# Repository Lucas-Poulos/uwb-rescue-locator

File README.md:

# UWB Rescue Locator

Repo: https://github.com/Lucas-Poulos/uwb-rescue-locator

A two-board UWB positioning system for a rescue/safety use case: a
**wristband** worn by a person, and a fixed **bay station** that locates it
in 3D from four anchor points and reports it over Bluetooth LE to a nearby
laptop.

Positioning is a **hybrid of two-way ranging and TDoA**, not symmetric
multilateration. A center anchor ranges to the tag for distance; three outer
anchors timestamp the same tag transmission and give direction from the
arrival-time differences. The four anchors are **not interchangeable** --
see [`docs/positioning.md`](docs/positioning.md), which is the document to
read first if you're working on anchors, clocking, coax, or connectors.

## Getting started (new contributor setup)

### 1. Install KiCad

The team standard is **KiCad 10.0.5** (see Toolchain below for why).

- **macOS**: `brew install --cask kicad` (Homebrew). If KiCad is already
  installed some other way, add `--force` to overwrite it.
- **Windows/Linux**: download the installer for your platform from
  https://www.kicad.org/download/.

You do **not** need to set any environment variables or configure library
paths yourself -- both boards' `fp-lib-table`/`sym-lib-table` use
`${KIPRJMOD}`-relative paths into this repo's own `shared/` and `libs/`
folders, so cloning the repo anywhere and opening a project just works.

The very first time you launch the KiCad GUI on a given machine, it may
offer to set up its own default global libraries (Device, Connector, etc.)
-- accept the defaults. This is a one-time, per-machine, KiCad-level setup
step, unrelated to this repo.

### 2. Get repo access and clone it

Ask whoever's administering the repo to add you as a collaborator (repo
link at the top of this file), then:

```
git clone git@github.com:Lucas-Poulos/uwb-rescue-locator.git
cd uwb-rescue-locator
```

(Use the HTTPS clone URL instead if you haven't set up an SSH key with
GitHub.)

### 3. Open a board

KiCad doesn't support one project spanning multiple PCBs, so open whichever
board you're working on directly -- there's no single top-level project
file for the whole repo:

```
open wristband/wristband.kicad_pro       # macOS; or just double-click the file
open bay-station/bay-station.kicad_pro
```

### 4. Sanity-check your setup

From a terminal, **outside** this repo (see the `kicad-cli` gotcha further
down for why):

```
cd /tmp
kicad-cli sch erc /path/to/uwb-rescue-locator/wristband/wristband.kicad_sch
```

If this reports a handful of known/expected items (see each board's sheet
table below) rather than a wall of "library not included in configuration"
errors, your KiCad install is set up correctly. If you do see that wall of
errors, see the per-major-version global library table note in Toolchain.

Before pushing anything, also read `CONTRIBUTING.md` -- branch off `main`,
don't edit a sheet someone else is actively working on, and PRs need review
(branch protection is on).

## Status (last updated 2026-11-06)

**Schematic capture is in progress on both boards.** Each board's Power/BMS
sheet is wired. The bay station's Regulation and Programming/Debug sheets
are now partially wired (grounds tied, some signal paths still open as of
2026-09-29) -- see the per-sheet table below. Everything else is still
placement-only. If you're an agent or a new teammate picking this up cold,
read this whole section before touching anything -- it's written to be a
complete handoff.

> ### Architecture change in flight: the bay station's anchors
>
> The positioning scheme was specified properly for the first time on
> 2026-09-19 (`docs/positioning.md`), and it invalidates how the bay
> station's UWB anchors are currently drawn. **Target: 10-30 cm accuracy at
> ~10 m, on Channel 5 (6489.6 MHz).**
>
> What the schematic gets wrong today:
>
> 1. **The four anchors are drawn as interchangeable peers.** They aren't --
>    one is a center anchor doing two-way ranging, three are outer anchors
>    doing TDoA against it.
> 2. **The antennas are on the board.** TDoA bearing accuracy scales with
>    baseline; a board-sized baseline gives ~17 degrees of bearing error.
>    The four antennas move onto ~1-2 m coax runs to a rigid frame.
> 3. **The DWM3000 module can't do TDoA in a multi-anchor array at all.** It
>    exposes no clock pin, so four of them cannot share a time base -- and
>    1 ns of clock error is 30 cm of position error.
>
> **The resolved architecture:** four discrete **DW3210** ICs on the one PCB,
> sharing a single 38.4 MHz TCXO through a 1:4 low-skew buffer, with the four
> antennas remote on coax. This makes synchronization *structurally absent*
> rather than solved -- no drift model, no sync firmware -- and moves the cost
> into the RF path, where CH5's ~17 dB of link margin absorbs it.
>
> Going discrete adds an RF front-end and a controlled-impedance stackup. It
> also loses the module's pre-certified status -- which **does not matter
> here**: this is a university prototype, not marketed or sold, so it doesn't
> go through FCC/CE testing. That was the single largest cost of going
> discrete, and it's now off the table. See `docs/decisions.md`.
>
> The remaining critical-path item is **array calibration**, which the design
> genuinely does not close without.
>
> **The wristband is unaffected by the clock problem** -- a single transceiver
> has nothing to synchronize against. It has separately consolidated onto a
> single DWM3001C; see its own README.

### What exists, per board

The wristband has 7 hierarchical sheets, the bay station 10. Reference designators are
project-wide unique per board (checked, no collisions) -- see each
`libs/components.csv` for the full part-by-part BOM.

**Wristband** (`wristband/`):
| Sheet | Status | Contents |
|---|---|---|
| Power BMS | **Wired** (global labels, no drawn wires), ERC clean (0 errors, 1 cosmetic warning) | JST-PH battery -> AO3401A reverse-polarity FET -> TVS -> DW01A+FS8205A protection -> MCP73831 charger (USB-C in) |
| Radio MCU | Placement only, not wired | DWM3001C (U3) + decoupling. One module: DW3110 UWB + nRF52833 MCU + accelerometer + both antennas |
| Mechanical | Placement only | 4x M2 mounting holes |
| Regulation | Placement only, not wired | MCP1700T-3302E/TT LDO (3.3V) -- battery hits 4.2V, DWM3001C tops out at 3.6V |
| Programming/Debug | Placement only, not wired | ARM Cortex Debug SWD header, targeting the nRF52833 inside U3 |
| Indicators | Placement only | Status LEDs: D2 charge (MCP73831 STAT) + D3 system (nRF52833 GPIO) |
| Test Points | Placement only, **new** | TP1-TP5: both rails, 2x GND, firmware timing marker |

**Bay Station** (`bay-station/`):
| Sheet | Status | Contents |
|---|---|---|
| Power BMS | **Wired** (global labels), ERC has 8 known/expected items (see `power_bms_notes.md`) | Barrel jack + USB-C power-only input -> MCP73871 power-path charger -> MAX17048 fuel gauge; separate backup-battery input with its own AO3401A reverse-polarity FET + TVS |
| Connectivity | Placement only, not wired | Fanstel BT840 (U3, nRF52840) + decoupling. Symbol authored from the real datasheet |
| UWB Array | Placement only, not wired | 4x DW3210 (U4=A0 center, U5-U7=A1-A3 outer) + GPIO5/6 straps (R10-R17) + IRQ pulldowns (R25-R28) + full per-anchor decoupling from Qorvo Figure 32 (C40-C74, FB1-FB4 beads, R33-R36 RF2 terminations) |
| Mechanical | Placement only | 4x M3 mounting holes |
| Regulation | **Partially wired** (11 wires, 3 junctions, 5 GND symbols added 2026-09-29); U8's VIN, EN, and PG still unconnected (ERC) | TPS62A02PDDCR buck converter -- steps the unregulated `+VSYS` rail down to a safe ~3.3V for the BT840 host and the DW3210 anchors |
| Clock Distribution | Placement only, **new** | Shared 38.4MHz reference for the 4x DW3210 array: AC-coupling + XTO caps placed, TCXO/buffer TBD |
| Indicators | Placement only | Status LEDs: D4 charging, D5 charge-done, D6 power-good (all MCP73871), D7 system (host GPIO) |
| Test Points | Placement only | TP1-TP21: rails, 2x GND, TCXO + 4x anchor clock, SPI bus, reset, per-anchor CS x4 + IRQ x4 |
| GNSS / Orientation | Placement only, **new** | MAX-M10S GNSS (U9) + LIS3MDL magnetometer (U10) + LIS2DH accelerometer (U11) -- georeferences the array |
| Programming/Debug | Placement only in practice (1 wire, 1 junction, 1 GND symbol added 2026-09-29 -- just the ground tie) | **Rebuilt for Nordic**: SWD header (J3) + RESET button (SW2), both still fully unwired per ERC. ESP32 circuitry and the second USB-C deleted |

"Placement only" sheets deliberately show a lot of ERC "not connected"/"not
driven" warnings -- that's expected, not a bug, until they get wired.

### Confirmed chips/ICs (all sourced against real datasheets, not guessed)

| Part number | Role | Board(s) | Qty |
|---|---|---|---|
| Qorvo **DWM3001C** | UWB transceiver + nRF52833 MCU + LIS2DH12 accelerometer + both antennas, one module. Replaced NINA-B111 + DWM3000 + the antenna sheet | Wristband | 1 |
| Qorvo **DW3210** | Discrete UWB transceiver IC, QFN-40 5x5mm. One per anchor (U4=A0 center, U5-U7=A1-A3 outer). Chosen over the DWM3000 module because the module exposes no clock pin, and a shared reference is what makes the TDoA array work -- see `docs/positioning.md` | Bay Station | 4 |
| Qorvo **DWM3000** | UWB transceiver module. **No longer used on either board** -- the wristband moved to the DWM3001C and the bay station to discrete DW3210. Symbol and footprint are retained in `shared/` for reference only | -- | 0 |
| Microchip **MCP73831** | LiPo linear battery charger | Wristband | 1 |
| Fortune Semiconductor **DW01A** | Battery protection IC | Wristband | 1 |
| Fortune Semiconductor **FS8205** (commonly sold as "FS8205A" -- see `wristband/libs/README.md`) | Protection dual MOSFET, DW01A's partner IC | Wristband | 1 |
| AOS **AO3401A** | Reverse-battery-polarity protection P-MOSFET ("ideal diode") | Wristband + Bay Station | 2 |
| onsemi **ESD5B5.0ST1G** | TVS diode, battery/power-input protection | Wristband (1) + Bay Station (2) | 3 |
| Fanstel **BT840** (Nordic nRF52840) | Host MCU + BLE link to a laptop. Replaced ESP32-S3-WROOM-1 once the WiFi/internet requirement was dropped | Bay Station | 1 |
| Microchip **MCP73871** | Charge management + power-path IC | Bay Station | 1 |
| Maxim/Analog Devices **MAX17048** | Battery fuel gauge (SOC monitor) | Bay Station | 1 |
| Microchip **MCP1700T-3302E/TT** | LDO regulator (3.3V) -- battery rail can hit 4.2V, which exceeds the DWM3001C's 3.6V operating max without this | Wristband | 1 |
| TI **TPS62A02PDDCR** | Buck (switching) regulator -- same voltage-safety role as the wristband's LDO, sized for the bay station's higher combined load current | Bay Station | 1 |

Footprint caveats: MAX17048 is flagged `_PLACEHOLDER` in its footprint file
-- pin/electrical data is fully verified, but one land-pattern dimension
needs re-checking against the real datasheet figure before fab (see
`bay-station/libs/README.md`). The same caveat applies to the DWM3000
footprint retained in `shared/`, though nothing uses it now.

**No footprint assigned yet**: `U3` on both boards (BT840, 65 pins; and
DWM3001C, 48 pins), plus bay-station `L1` (1uH inductor -- no exact KiCad
default matches the XGL3520, pick at BOM time) and `SW2`. Not blocking
while both `.kicad_pcb` files are still empty, but it blocks layout.

Standard passive size for this whole project: **0603** for R/C/L (0-ohm
0603 link/jumper resistors are documented as a standard available option in
each `components.csv`, not yet placed on any sheet -- no specific
strap/bridge need identified yet).

Full reasoning/history for every choice above, plus the still-open
decisions (anchor placement, uplink backend, etc.), is in
`docs/decisions.md`.

### Known gotchas for whoever (human or agent) works on this next

- **kicad-cli silently fails on `extends`-based symbols.** Any cached
  schematic symbol using KiCad's `extends` mechanism (e.g. the default
  `AO3401A extends TP0610T`) makes `kicad-cli` fail to load the *entire
  file* and silently report it as empty (0 components, 0 ERC violations)
  rather than erroring loudly. Both boards work around this by embedding a
  flattened, non-`extends` copy of AO3401A. If a future sheet adds another
  `extends`-based part and ERC suspiciously shows 0 violations, check this
  first.
- **Always run `kicad-cli` from a scratch directory, never from inside a
  git repo.** It writes `.rpt` report files to the current working
  directory as a side effect; running it from inside a repo pollutes that
  repo's working tree with stray files.
- **KiCad's global library table is per-major-version and doesn't
  auto-populate from `kicad-cli` alone** -- see the Toolchain section below.
- **Don't leave a KiCad GUI window open on a project while also editing its
  files by hand/via script.** This happened once already: a background GUI
  session silently resaved `bay-station/power_bms.kicad_sch` in KiCad 10
  format while a concurrent edit was adding new sheets to the root file. No
  data was lost (verified via a reference-designator diff before
  committing), but it could have silently clobbered the newer edits if the
  stale window had been saved again afterward. Close/reload any open KiCad
  windows before doing further programmatic edits, and vice versa.
- The sibling project at `~/kicad-projects/wristband-alarm` (a *different*,
  unrelated wristband-alarm concept, also u-blox NINA-based) has its own
  long-standing uncommitted working-tree state -- don't touch it, don't
  assume its README reflects its actual working tree.

### In-flight work on GitHub (as of 2026-11-06)

Merged into `main` today: this Design Specifications section, the bay
station's power/regulation/programming-debug wiring pass, the decision not
to add an external wristband IMU (`docs/decisions.md` -- the DWM3001C's
built-in LIS2DH12 covers it), PR #9 (the bay station's missing I2C pull-ups,
R37-R39), and PR #8 (the full per-anchor DW3210 decoupling set, C40-C74 +
FB1-FB4 + R33-R36, from Qorvo's own reference design).

#8 and #9 both textually conflicted with the power-wiring pass on
`bay-station/connectivity.kicad_sch` and `uwb_array.kicad_sch` respectively,
because those files got reserialized to KiCad 10 format in between. Each was
hand-ported onto the reserialized files rather than text-merged -- see
`b7ab51f` and `4ef1099` for exactly what that involved and how it was
verified (balanced parens, no duplicate references, ERC recognizing every
new component with precisely the expected violation delta). This is the one
case where resolving a KiCad schematic conflict by hand was done carefully
and checked, not the norm -- `CONTRIBUTING.md`'s warning about silent
corruption from hand-resolving `.kicad_sch` conflicts still stands for
anything less thoroughly verified.

One PR needs a **team decision, not a merge**: **#7**
`feat/bay-station-wifi` adds an ESP32-C5 Wi-Fi co-processor and explicitly
reopens part of the 2026-09-19 "no WiFi" call (see `docs/decisions.md`,
"Bay-station Wi-Fi uplink"). Its own GPIO allocation table is marked
"PROPOSED, needs team sign-off" -- read that section before merging it.

### Not done yet (in rough next-up order)

1. **Bay station: rework the anchor design** for four discrete DW3210s on
   one board sharing a TCXO, with the antennas on coax. Blocked behind the
   open items in `docs/decisions.md` (cable loss, TCXO/buffer selection,
   array calibration) -- this is the project's critical path.
2. Wire all placement-only sheets (net labels between MCU/radio pins, their
   decoupling, the new regulator outputs, and power-rail connections in
   from Power BMS). The wristband can proceed independently of item 1.
3. ~~**Bay station: resolve the two-USB-C-connector situation**~~ -- resolved
   by the move to Nordic. The second connector existed only for ESP32-S3
   native-USB flashing; the BT840 programs over SWD, so it goes away with the
   rest of the ESP32-specific circuitry.
4. **Bay station: source a real footprint for L1** (the buck converter's
   inductor, Coilcraft XGL3520-102MEC) -- no KiCad-default match exists yet.
5. ~~Confirm/re-verify decoupling cap values against each part's exact
   datasheet application circuit~~ -- done, see `docs/passives-reference.md`.
   One passive was found missing (100k IRQ/GPIO8 pulldowns, now added to all
   5 DWM3000 instances); DWM3000's own decoupling was confirmed to exceed
   what Qorvo's minimal example circuit actually calls for (kept anyway, not
   wrong, just more conservative than strictly required).
6. ~~Antenna matching-network values~~ -- gone. The DWM3001C carries both
   antennas on-module, so `antenna.kicad_sch` was deleted along with the
   tuning task.
7. ~~Anchor placement/enclosure geometry~~ -- topology resolved (all four
   transceivers on-board, antennas remote on coax to a rigid frame, see
   `docs/positioning.md`); the remaining piece is the frame's mechanical
   design, including A0's out-of-plane offset.
8. Bay station uplink protocol -- what the laptop actually receives over BLE
   (open decision). "Backend" no longer applies: there is no server, see
   `docs/system-overview.md`.
9. PCB layout. The bay station's `.kicad_pcb` has its **4-layer
   controlled-impedance stackup** set from DW3000 Section 7.3.2 Figure 35
   (1.048mm finished) but is otherwise still genuinely empty: 0 footprints,
   no outline. Blocked upstream, same as before -- the schematic is mostly
   placement-only, so there's nothing to import yet.

   **Correction, 2026-11-06: the wristband's `.kicad_pcb` is not an empty
   stub.** It already carries 36 footprints, a routed board outline, and
   real DRC findings (100 unrouted ratsnest items, plus silkscreen/clearance
   violations) from the DWM3001C migration (PR #5, merged). U3 (the
   DWM3001C itself) has no footprint assigned yet, so it isn't among those
   36 and can't be placed until one is imported -- see the footprint-caveats
   note above.

## System overview

```
                         A1 ← antenna on coax
                            \
   ┌─────────────┐           \      ┌───────────────────────────┐
   │  Wristband   │  UWB       ○────│  Bay Station (ONE PCB)     │
   │  (worn tag)  │ ═════════▶ A0   │  4x DW3210, one TCXO       │
   └─────────────┘  one TX    / \   │  BT840 (nRF52840) host     │
                             /   \  └───────────┬────────────────┘
                           A2     A3            │ Bluetooth LE
                      antennas on ~1-2 m        ▼
                      coax, rigid frame       Laptop

   A0     two-way ranging  -> range to tag
   A1-A3  TDoA vs. A0      -> direction to tag

   All four transceivers share one clock on the board.
   Only the antennas are remote.
```

- **Wristband**: one Qorvo DWM3001C (UWB + nRF52833 MCU + antennas) +
  a compact BMS (MCP73831 charger + DW01A/FS8205 protection + AO3401A
  reverse-polarity protection). Design compromises favor small size and
  just enough battery life to get core functionality working. In the
  positioning scheme its job is simply to transmit -- one transmission
  yields all four measurements, deliberately, because the tag is the
  power-constrained side.
- **Bay station**: four UWB receivers in two roles (one center, three outer)
  on a single PCB sharing one TCXO + a Fanstel BT840 (nRF52840) host, linking
  to a laptop over BLE + a BMS designed for long runtime rather than small size
  (MCP73871 power-path charger + MAX17048 fuel gauge), since the bay station
  isn't worn. The four antennas sit on ~1-2 m coax runs to a rigid frame --
  that's what buys the baseline the bearing measurement needs.

There's no physical connector between the wristband and the bay station --
their only interface is the UWB radio link. The bay station's own antennas
are wired to it over SMA coax (CH5 at 6489.6 MHz is above U.FL's 6 GHz
rating). See `docs/system-overview.md` and `docs/positioning.md`.

## Design specifications

Quick-reference only -- full reasoning, error budgets, and datasheet
citations live in `docs/positioning.md` (RF/clock/mechanical) and
`docs/decisions.md` (every component/architecture call). Anything not listed
here as resolved is still an open decision; check there before assuming a
number is final.

**Performance target**
| | |
|---|---|
| Accuracy | 10-30 cm |
| Range | ~10 m |
| Baseline (A0-to-outer-antenna spacing) | ~1 m as built; frame size is the real limit, not cable loss |

**RF**
| | |
|---|---|
| UWB channel | Channel 5, 6489.6 MHz |
| UWB IC, bay station | 4x Qorvo DW3210 (QFN40, non-PDoA) -- U4=A0 center, U5-U7=A1-A3 outer |
| UWB IC, wristband | Qorvo DW3110 (WLCSP), inside the DWM3001C module |
| UWB connectors | SMA -- CH5 is above U.FL/W.FL/MMCX/MCX's 6 GHz rating and SMB's 4 GHz rating |
| Link budget | 86 dB available (CH5, 850 kbps, 1024-symbol preamble); ~17 dB margin at 10 m |
| Antennas (bay station) | Not yet selected -- candidates covering CH5: Taoglas UWC.01 / ILA.68 / UWCCP.01 |

**Clock (bay station array)**
| | |
|---|---|
| Reference | One 38.4 MHz TCXO -> 1:4 low-skew fan-out buffer -> all 4 DW3210 XTI pins |
| Coupling | 2200 pF AC-coupled into each XTI; 1 pF from each XTO to ground |
| TCXO spec | 0.8 V-VDD2 Vpp, -132 dBc/Hz @ 1 kHz, -145 dBc/Hz @ 10 kHz, 40-60% duty (DW3000 Datasheet Table 10) |
| TCXO + buffer part numbers | Open |

**Positioning architecture**
Hybrid two-way-ranging + TDoA, not symmetric multilateration -- see
`docs/positioning.md` for the full derivation.
| | |
|---|---|
| Center anchor (A0) | Two-way ranging with the wristband -> range |
| Outer anchors (A1-A3) | TDoA vs. A0 on the same tag transmission -> direction |
| System | 4 equations, 3 unknowns -- overdetermined by 1; use the residual as a quality metric |
| Mechanical | Rigid frame fixes geometry (no install-time survey); A0 offset 20-30 cm out of the A1-A3 plane to avoid a mirror ambiguity |
| Array calibration | Required, not optional (generic +/-6 cm spec is 3x too loose at this baseline); procedure/fixture still open |

**Power**
| | Wristband | Bay station |
|---|---|---|
| Regulator | TI TPS7A0233PDBVR LDO, 3.3V | TI TPS62A02PDDCR buck, 2A |
| Load vs. rating | ~43 mA (4.6x headroom) | ~347-682 mA depending on estimate (3-6x headroom; recheck once clock parts are chosen) |
| Standby | ~2.7 uA | n/a -- BMS optimized for runtime, not size |

**Connectivity**
| | |
|---|---|
| Wristband <-> bay station | UWB only -- one tag transmission per exchange, no other radio link |
| Bay station -> laptop | Bluetooth LE (GATT service) -- no WiFi, no internet uplink |
| Georeferencing | u-blox MAX-M10S GNSS + ST LIS3MDL magnetometer + ST LIS2DH accelerometer (bay station only; position + heading both required) |

**Cost** (one prototype pair, hobbyist qty-1 pricing -- see `docs/bom-cost.md`)
| | |
|---|---|
| Wristband | ~$67 |
| Bay station | ~$278 |
| Total | ~$345 |

**Regulatory**
No FCC/CE certification -- university prototype, not sold or deployed as a
product. Revisit as a first-class schedule item if that ever changes.

**Toolchain**
| | |
|---|---|
| KiCad | 10.0.5 (files on disk still in 8.0 format) |
| MCUs | Both Nordic -- nRF52833 (wristband, inside DWM3001C) / nRF52840 (bay station, inside the Fanstel BT840) |
| Firmware SDK | Open -- nRF5 SDK vs. Zephyr / nRF Connect SDK |

## Repo layout

```
shared/                      # symbols/footprints/3D models used on BOTH boards (e.g. the UWB IC)
  symbols/                   # shared .kicad_sym library
  footprints/                # shared .pretty footprint library
  3dmodels/                  # shared .step/.wrl models
wristband/                   # KiCad project: the wearable tag
  wristband.kicad_pro/sch/pcb
  libs/                      # wristband-only symbols/footprints
bay-station/                 # KiCad project: the fixed 4-anchor station
  bay-station.kicad_pro/sch/pcb
  libs/                      # bay-station-only symbols/footprints
docs/
  positioning.md             # the ToF + TDoA scheme, error budget, clock architecture
  system-overview.md         # block diagram + RF/data interface between the boards
  decisions.md               # open + resolved component/architecture decisions log
  passives-reference.md      # every chip's reference-design passives, compiled per-chip
  bom-cost.md                # build cost estimate for one prototype pair
firmware/                    # nRF52840 / nRF52833 firmware -- skeleton only, nothing written
CLAUDE.md                    # working rules for Claude Code / other coding agents
CONTRIBUTING.md              # git workflow, sheet conventions, pre-push checks
```

Each board is its own KiCad project (KiCad doesn't support one project
spanning multiple PCBs), but both live in this one repo so shared parts,
docs, and history stay in one place. Each project's `fp-lib-table` /
`sym-lib-table` reference the `shared/` libraries via `${KIPRJMOD}` relative
paths, so this works regardless of where the repo is cloned -- no per-machine
setup needed.

## Toolchain

Files are currently in **KiCad 8.0** format, originally authored/verified
against KiCad 8.0.6. As of 2026-08-14 this machine has been upgraded to
**KiCad 10.0.5** (the actual current stable -- confirmed as the team's
standard, superseding an earlier, since-corrected plan to target KiCad 9.x).
All existing files were re-checked with
`kicad-cli` under 10.0.5 (`sch erc`/`pcb drc`) and open/parse cleanly with no
new issues -- opening a file in the newer GUI and re-saving is still a
one-way, zero-cost upgrade whenever the team wants to bump the file format
itself; nothing has been re-saved yet, so the files on disk are still 8.0
format.

Note for anyone else upgrading KiCad's major version: `kicad-cli` alone
won't auto-populate the new version's global symbol/footprint library table
(`~/Library/Preferences/kicad/<version>/sym-lib-table` /`fp-lib-table`) --
that normally happens the first time you launch the actual KiCad GUI and it
offers to migrate/create settings. If you only ever use `kicad-cli`
headlessly without opening the GUI first, you may see a wall of spurious
"library not included in configuration" ERC errors -- just launch KiCad.app
once (or copy the two `*-lib-table` files from
`.../KiCad.app/Contents/SharedSupport/template/`) to fix it.

## Using Claude Code (or another coding agent) on this project

**The working rules for agents live in [`CLAUDE.md`](CLAUDE.md)** -- Claude
Code picks that up automatically. This section is the human-readable version
of why those rules exist.

KiCad's file formats (`.kicad_sch`, `.kicad_pcb`, `.kicad_pro`, `.kicad_sym`,
`.kicad_mod`) are plain text (S-expression or JSON) -- an agent can read and
edit them directly like any other source file, no special MCP server or
plugin required. Everything in this repo so far was built that way. A few
things make it work reliably, several of them learned the hard way in this
repo's own history:

- **`kicad-cli` is the fast headless sanity check.** After any edit, run
  `kicad-cli sch erc <board>.kicad_sch` and `kicad-cli pcb drc
  <board>.kicad_pcb` before trusting a change.
  - **macOS**: a Homebrew install symlinks it onto `PATH` automatically
    (`/opt/homebrew/bin/kicad-cli`); otherwise it's inside the app bundle at
    `/Applications/KiCad/KiCad.app/Contents/MacOS/kicad-cli`.
  - **Windows**: the official installer puts it on `PATH` automatically; if
    not, it's at `C:\Program Files\KiCad\10.0\bin\kicad-cli.exe`.
  - **Linux**: on `PATH` automatically via most package managers (apt,
    dnf, etc.) or the official AppImage/flatpak.
- **Always run `kicad-cli` from a scratch/temp directory, never from
  inside this repo.** It writes `.rpt` report files to the current working
  directory as a side effect -- running it from inside a git repo (this
  one or any other) pollutes the working tree with stray files. This has
  actually happened once already, to an unrelated sibling project, from a
  leftover `cd`.
- **`kicad-cli` silently fails on `extends`-based symbols.** A cached
  schematic symbol using KiCad's `extends` mechanism (e.g. the default
  library's `AO3401A extends TP0610T`) makes `kicad-cli` fail to load the
  *entire file* and report it as empty (0 components, 0 ERC violations)
  instead of erroring loudly -- a suspiciously clean ERC run is a red flag,
  not necessarily good news. This repo works around it everywhere by
  embedding flattened, non-`extends` copies of any such symbols (see
  `docs/decisions.md` and the various `*_notes.md` files for examples).
- **Use an existing sheet/symbol/footprint as the format template before
  writing a new one.** Every file in this repo was built by reading a
  known-good file first -- either one already in this repo, or one of
  KiCad's own bundled default libraries -- and matching its exact
  structure, rather than freehand-authoring the s-expression format from
  memory. This repo uses literal tab characters for indentation, not
  spaces; match that.
- **Don't run scripted file edits at the same time as a live KiCad GUI
  session has the same project open.** A background GUI window doesn't
  know about changes made outside it, and saving from a stale window can
  silently overwrite newer edits -- this already caused one near-miss on
  the bay station board (see "Known gotchas" above). Close/reload any open
  KiCad windows before scripted edits, and vice versa. A lock file at
  `<board>/~<board>.kicad_pro.lck` means a GUI session currently has that
  project open.
- **Verify real datasheet facts (pinouts, voltage ratings, current draw)
  by actually fetching and reading the datasheet PDF**, not from memory or
  a search-result summary -- several real bugs/gaps in this repo were only
  caught this way (e.g. the wristband's missing voltage regulator, a
  part-number that doesn't actually exist, a mislabeled SOT-23-6 part).
- **pcbnew's Python bindings** are available for programmatic
  footprint/board work (generating a blank `.kicad_pcb`, loading a
  footprint to sanity-check its pad count, etc.) via KiCad's own bundled
  Python interpreter -- **not** your system Python, which won't have the
  `pcbnew` module installed:
  - **macOS**: `/Applications/KiCad/KiCad.app/Contents/Frameworks/Python.framework/Versions/Current/bin/python3`
  - **Windows**: typically `C:\Program Files\KiCad\10.0\bin\python.exe`
  - **Linux**: usually just your system `python3` if KiCad was installed via
    a package manager that wires up the `pcbnew` module for it; otherwise
    check your distro's KiCad packaging docs.

## Will this work on both Mac and Windows?

Yes, and this has actually been checked, not just assumed:

- No absolute Mac-specific paths are baked into any `.kicad_pro`/`.kicad_sch`/
  `.kicad_pcb`/library file (`git grep`-checked) -- all cross-file/library
  references use `${KIPRJMOD}`-relative paths, which KiCad resolves
  identically on every OS.
- No filenames in this repo use characters or reserved names that are
  illegal on Windows (`: * ? " < > |`, or `CON`/`PRN`/`AUX`/`NUL`/`COM1-9`/
  `LPT1-9`), and no path exceeds even a fraction of Windows' historical
  260-character path limit (longest path in this repo is 80 characters).
- All tracked files use consistent LF line endings, and `.gitattributes`
  normalizes this going forward so a Windows contributor's git config
  (which sometimes auto-converts line endings on checkout) can't silently
  turn KiCad files into CRLF and create noisy diffs or merge pain.

What differs by platform is purely the install step and a couple of tool
paths (both covered above/in Getting Started) -- KiCad itself, the file
formats, and this repo's structure are fully cross-platform.

## Contributing

See `CONTRIBUTING.md` for the git workflow (branching, hierarchical-sheet
conventions to avoid merge conflicts, pre-push checks).

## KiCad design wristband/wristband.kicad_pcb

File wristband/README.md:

# Wristband

The worn tag. Open `wristband.kicad_pro` in KiCad.

## Scope

Deliberately minimal: **battery management plus one UWB module, and not much
else.** The tag's only job is to take part in a two-way ranging exchange with
the bay station's center anchor. Everything not needed for that is gone.

- **UWB + MCU**: Qorvo **DWM3001C** (resolved 2026-09-19) -- one module
  containing the DW3110 UWB transceiver, a Nordic nRF52833 MCU, an ST
  LIS2DH12 accelerometer, the UWB and Bluetooth antennas, power management
  and the 38.4 MHz crystal. Its datasheet states it *"requires no RF design
  as the antenna and associated analog and RF components are on the module"*.
- **BLE and the accelerometer are unused.** The tag talks only over UWB. Both
  are silicon inside a module bought for its Cortex-M4 and its UWB radio --
  they cost nothing to leave idle: no external parts, no wiring, no firmware.
  See "Worth revisiting" below.
- **BMS**: sized for "just enough" runtime -- size and weight take priority
  over battery life here, in contrast with the bay station.

Why the tag transmits once per fix: the bay station's center anchor completes
the ranging exchange, and the three outer anchors timestamp that *same*
transmission. One transmission, four measurements -- deliberately, because
the tag is the power-constrained side. See `../docs/positioning.md`.

## Status

Seven hierarchical sheets, all registered in `wristband.kicad_pro`'s `sheets`
list and wired into `wristband.kicad_sch` as sheet symbols.

| Sheet | Status | Contents |
|---|---|---|
| `power_bms` | **Wired** (global labels, no drawn wires), ERC clean | Full battery/charging/protection chain |
| `radio_mcu` | **Wired**, ERC clean | DWM3001C (U4) + decoupling; SWD, RESET_N, SWO, VBAT_SENSE, SOS button |
| `regulation` | **Wired**, ERC clean | TPS7A0233PDBVR LDO -> 3.3V (U5) |
| `programming_debug` | **Wired**, ERC clean | ARM Cortex Debug SWD header |
| `indicators` | Placement only -- **8 ERC errors** (unconnected pins) | Status LEDs D2 (charge) + D3 (system) |
| `testpoints` | Placement only -- **5 ERC errors** (unconnected pins) | TP1-TP5: both rails, 2x GND, firmware timing marker |
| `mechanical` | Placement only | 4x M2 mounting holes |

**"Placement only" means components are instantiated and laid out, but
nothing is wired** -- no drawn wires, no global labels, no net identity.

`indicators` and `testpoints` are the two sheets still in that state. They
came across from the positioning-architecture redesign on `main`, where they
were never wired, and they account for all 13 of the wristband's remaining
ERC errors. Everything else on this board is wired and ERC clean.

**ERC, re-run 2026-11-06 with kicad-cli 10.0.5: 16 violations (13 of them
`error` severity, not "ZERO errors" as this line used to claim -- stale
since before the sheets above got wired).** 13 pin_not_connected (the two
sheets still placement-only, `indicators` and `testpoints`) plus 3
lib_symbol_mismatch from the embedded 8.0-format symbol copies differing
from the 10.x libraries (pre-existing and by design -- see the
flattened-copy workaround in `../CLAUDE.md`).

**DRC, re-run 2026-11-06: 210 violations.** This line also used to say "one
violation, `invalid_outline`, because no board outline is drawn yet" --
stale since PR #5 landed the actual PCB (36 footprints, a real outline).
Current breakdown: 100 unconnected_items (the unrouted ratsnest -- expected,
nothing is routed yet), 91 silk_over_copper, 71 silk_overlap, 33
via_dangling, 10 copper_edge_clearance, 3 silk_edge_clearance, 2 clearance.
The silk_over_copper/silk_overlap counts jumped from 57/7 on 2026-11-06 when
every footprint's Value was moved from hidden-on-F.Fab to visible on
F.SilkS (see `docs/decisions.md`) -- expected and accepted: 0402/0603
passive values often don't fit silkscreen cleanly, and resolving the
overlaps is layout work, not a reason to hide the values again.

### Sheet detail

- **`power_bms.kicad_sch`** -- the complete battery chain: 2-pin JST-PH
  battery input (`BT1`); AO3401A P-MOSFET reverse-polarity "ideal diode"
  (`Q1`, `R1`); battery-rail TVS ESD5B5.0ST1G (`D1`); DW01A + FS8205A
  single-cell overcharge/overdischarge/overcurrent protection wired per
  Fortune Semiconductor's own DW01A typical application circuit (`U1`, `Q2`,
  `R2`, `R3`, `C1`); MCP73831 Li-Po charger with power-only USB-C input, PROG
  resistor sized for ~147mA charge current, and datasheet-recommended
  input/output caps (`U2`, `J1`, `R4`, `C2`, `C3`, `R5`, `R6`); bulk/bypass
  decoupling on the protected `VBAT` rail (`C4`, `C5`).

  Net identity is carried entirely by global labels placed on top of each
  pin. ERC: 0 errors, 1 harmless documented warning. Full rationale in
  `power_bms_notes.md`.

- **`radio_mcu.kicad_sch`** -- one `wristband:DWM3001C` (`U4`) plus VDD
  decoupling (`C6` 100nF, `C7` 10uF). Now wired: SWD (`SWDCLK`/`SWDIO`/
  `SWO`), `RESET_N`, `VBAT_SENSE` on P0.02/AIN0, and the SOS button on
  P0.17. 12 of the module's 48 pins are tied; the rest await the pin
  assignments still open in `../docs/decisions.md`.

  Pin data verified against the real Qorvo DWM3001C Data Sheet Rev B (May
  2022), Table 2. One caveat carried in the symbol: **pin 18 is not
  documented in that table** (it lists 1-17 and 19-48), so it is modelled as
  a passive NC and needs confirming against the land-pattern figure.

  Decoupling values are conservative standard practice, *not*
  datasheet-specified -- the module has on-board power management and Qorvo
  publishes no external application circuit for it.

  Two real layout requirements are recorded in the sheet's own notes: the
  **10 mm antenna keep-out** (Section 7.1) and **keeping the module at least
  1 cm from the PCB edge** (Section 7.2), which reduces the horizontally
  polarized radiation component and improves multipath resilience.

- **`regulation.kicad_sch`** -- TI **TPS7A0233PDBVR** LDO (`U5`, SOT-23-5,
  3.3V fixed, 200mA, 25nA typ Iq) steps the protected `VBAT` rail (up to
  4.2V at full charge) down to `+3V3`. Replaced the MCP1700T-3302E/TT on
  2026-09-23, whose 1.6uA Iq had become the board's largest standby draw --
  see `../docs/decisions.md`. Still required: the DWM3001C's operating
  maximum is 3.6V (Table 4), well under a full battery. **EN must be tied
  high**; the part is disabled when EN floats. See `regulation_notes.md`.

- **`programming_debug.kicad_sch`** -- ARM Cortex Debug SWD connector (`J3`,
  `Connector:Conn_ARM_JTAG_SWD_10`, 2x5 1.27mm). Now targets the nRF52833
  inside U3, via `SWD_CLK` (pin 2) and `SWD_DIO` (pin 3).

- **`indicators.kicad_sch`** -- status LEDs. `D2`/`R10` is charge status from
  MCP73831 `STAT` (U2 pin 1, `power_bms.kicad_sch`). `D3`/`R11` is system
  status on an nRF52833 GPIO. 0603 parts, indicative 1k series resistors,
  low-current by design since the tag runs off a small cell.

- **`testpoints.kicad_sch`** *(new)* -- `TP1` +3V3, `TP2` VBAT, `TP3`/`TP4`
  ground, `TP5` a firmware timing marker on a spare nRF52833 GPIO so tag-side
  exchange timing is visible on a scope. Deliberately minimal: the DWM3001C's
  internals are unreachable and SWD already comes out on `J3`. `TP2` matters
  because there is no power switch -- it is the only way to check the battery
  chain without disconnecting the cell.

- **`mechanical.kicad_sch`** -- 4x M2 mounting holes (`H1`-`H4`).

### Next up

1. **Get U3's footprint.** Do not hand-author it -- import from a vendor
   library. Qorvo supplies DWM3001C footprint/symbol files (Altium format)
   via their UWB tech forum, and SnapMagic/SnapEDA lists a Qorvo-provided
   set. Check pad naming matches this symbol's 1-48 numbering. Blocks layout.
2. Wire the six placement-only sheets: the `VBAT` -> `+3V3` rail handoff,
   SWD to U3, the LED drives. There is no MCU-to-transceiver SPI to wire any
   more -- that link is inside the module.

### Worth revisiting

**Motion-gating the UWB.** The LIS2DH12 accelerometer inside the DWM3001C is
unused, but the tag is the power-constrained side of the whole system. Only
ranging when the wearer actually moves is the largest battery lever
available. Worth doing once basic ranging works.

An external IMU was proposed on 2026-09-28 and **rejected** -- the module
already carries an accelerometer, and adding a second one costs board area
and standby current on the one board that can least afford either. See
`../docs/decisions.md`. The one thing the LIS2DH12 cannot give you is
**angular rate**; if a gyro is ever genuinely required, that is a real gap
and reopens the question.

**One assumption here needs checking before anyone calls this free.** The
earlier wording said motion-gating "costs nothing in hardware". That is not
yet established. `I2C0_SDA` (pin 14) and `I2C0_SCL` (pin 15) are brought out
as module pins and are **unconnected in this schematic** -- a netlist export
confirms both sit on `unconnected-(...)` nets. Whether the LIS2DH12 is
reachable with no external parts depends on whether Qorvo fitted pull-ups
*inside* the module:

- If internal pull-ups exist, motion-gating really is firmware-only.
- If not, the bus needs two external pull-ups to `+3V3`, and "costs nothing
  in hardware" is wrong.

I2C is open-drain and cannot return to a logic high without a pull-up
somewhere, so one of those two must be true. Resolve it against the real
**DWM3001C Data Sheet Rev B (May 2022)** -- the same document the symbol in
`libs/` was authored from -- before planning firmware around it.

## Libraries

- `libs/` -- wristband-only symbols/footprints, including the hand-authored
  `DWM3001C` symbol
- `../shared/` -- still registered via `fp-lib-table`/`sym-lib-table`, but
  this board no longer uses anything from it (see `../shared/README.md`)

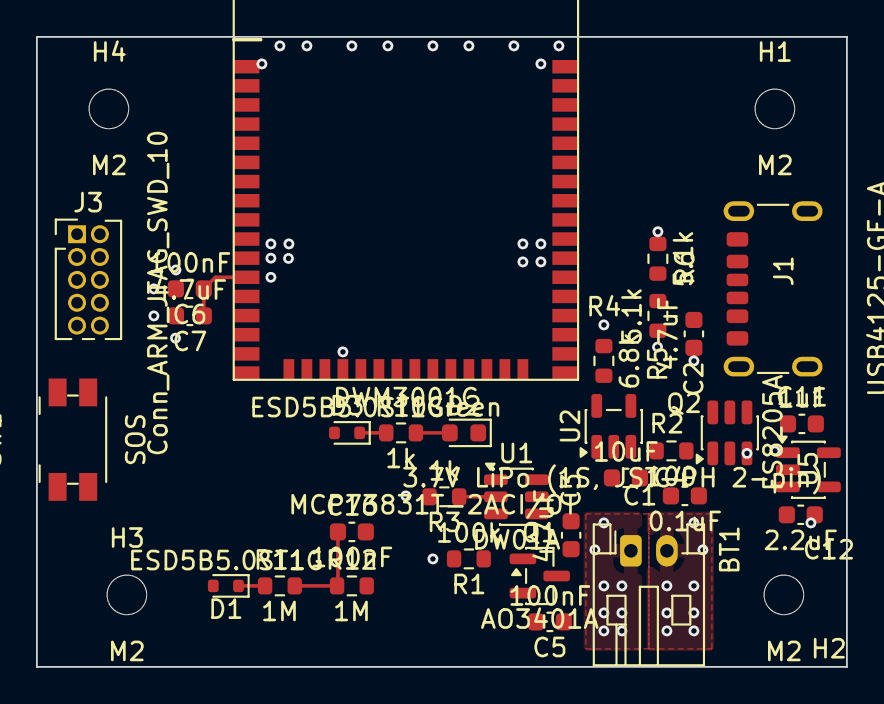
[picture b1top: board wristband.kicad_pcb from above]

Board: 4 copper layers, 45.0 x 35.0 mm, 36 parts (0 on the bottom side), 23 nets.

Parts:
BT1: 3.7V LiPo (1S, JST-PH 2-pin); JST_PH_S2B-PH-K_1x02_P2.00mm_Horizontal
C1: 0.1uF; C_0603_1608Metric
C2, C3, C7: 4.7uF; C_0603_1608Metric
C4: 10uF; C_0603_1608Metric
C5, C6, C16: 100nF; C_0603_1608Metric
C11: 1uF; C_0603_1608Metric
C12: 2.2uF; C_0603_1608Metric
D1, D3: ESD5B5.0ST1G; D_SOD-523
D2: Green; LED_0603_1608Metric
H1, H2, H3, H4: M2; MountingHole_2.2mm_M2
J1: USB4125-GF-A; USB_C_Receptacle_GCT_USB4125-xx-x_6P_TopMnt_Horizontal
J3: Conn_ARM_JTAG_SWD_10; PinHeader_2x05_P1.27mm_Vertical
Q1: AO3401A; SOT-23
Q2: FS8205A; SOT-23-6
R1: 100k; R_0603_1608Metric
R2: 100; R_0603_1608Metric
R3, R10: 1k; R_0603_1608Metric
R4: 6.8k; R_0603_1608Metric
R5, R6: 5.1k; R_0603_1608Metric
R11, R12: 1M; R_0603_1608Metric
SW1: SOS; Panasonic_EVQPUJ_EVQPUA
U1: DW01A; SOT-23-6
U2: MCP73831T-2ACI/OT; SOT-23-5
U4: DWM3001C; DWM3001C_PLACEHOLDER
U5: TPS7A0233PDBVR; SOT-23-5

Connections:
+3V3: C6.1, C7.1, C12.1, J3.1 (VTref), U4.12 (VDD), U5.5 (OUT)
/Radio MCU/SOS_BNT: SW1.1, U4.6 (P0.17)
CC1: J1.A5 (CC1), R5.1
CC2: J1.B5 (CC2), R6.1
CELL_N: BT1.2 (-), C1.2, Q2.1 (S1), U1.4 (TD), U1.6 (GND)
CELL_P: BT1.1 (+), Q1.2 (S)
CHG_PROG: R4.1, U2.5 (PROG)
CHG_STAT: D2.1 (K), U2.1 (STAT)
DW01A_VCC: C1.1, R2.2, U1.5 (VCC)
FS_D12: Q2.2 (D12), Q2.5 (D12)
GND: C2.2, C3.2, C4.2, C5.2, C6.2, C7.2, C11.2, C12.2, C16.2, D1.2 (A2), D3.2 (A2), J1.A12 (GND), J1.B12 (GND), J1.SH (SHIELD), J3.3 (GND), J3.5 (GND), J3.9 (GNDDetect), Q2.3 (S2), R1.2, R3.2, R4.2, R5.2, R6.2, R12.2, SW1.2, U2.2 (VSS), U4.1 (GND), U4.11 (GND), U4.21 (GND), U4.38 (GND), U4.48 (GND), U5.2 (GND)
unnamed: D2.2 (A), R10.2
PROT_CS: R3.1, U1.2 (CS)
PROT_OC: Q2.4 (G2), U1.3 (OC)
PROT_OD: Q2.6 (G1), U1.1 (OD)
Q1_GATE: Q1.1 (G), R1.1
RESET_N: J3.10 (~RESET), U4.47 (RESET)
SWDCLK: J3.4 (SWCLK/TCK), U4.2 (SWD_CLK)
SWDIO: J3.2 (SWDIO/TMS), U4.3 (SWD_DIO)
SWO: J3.6 (SWO/TDO), U4.28 (P1.00)
VBAT: C3.1, C4.1, C5.1, C11.1, D1.1 (A1), Q1.3 (D), R2.1, R11.1, U2.3 (VBAT), U5.1 (IN), U5.3 (EN)
VBAT_SENSE: C16.1, R11.2, R12.1, U4.46 (P0.02)
VBUS: C2.1, D3.1 (A1), J1.A9 (VBUS), J1.B9 (VBUS), R10.1, U2.4 (VDD)
